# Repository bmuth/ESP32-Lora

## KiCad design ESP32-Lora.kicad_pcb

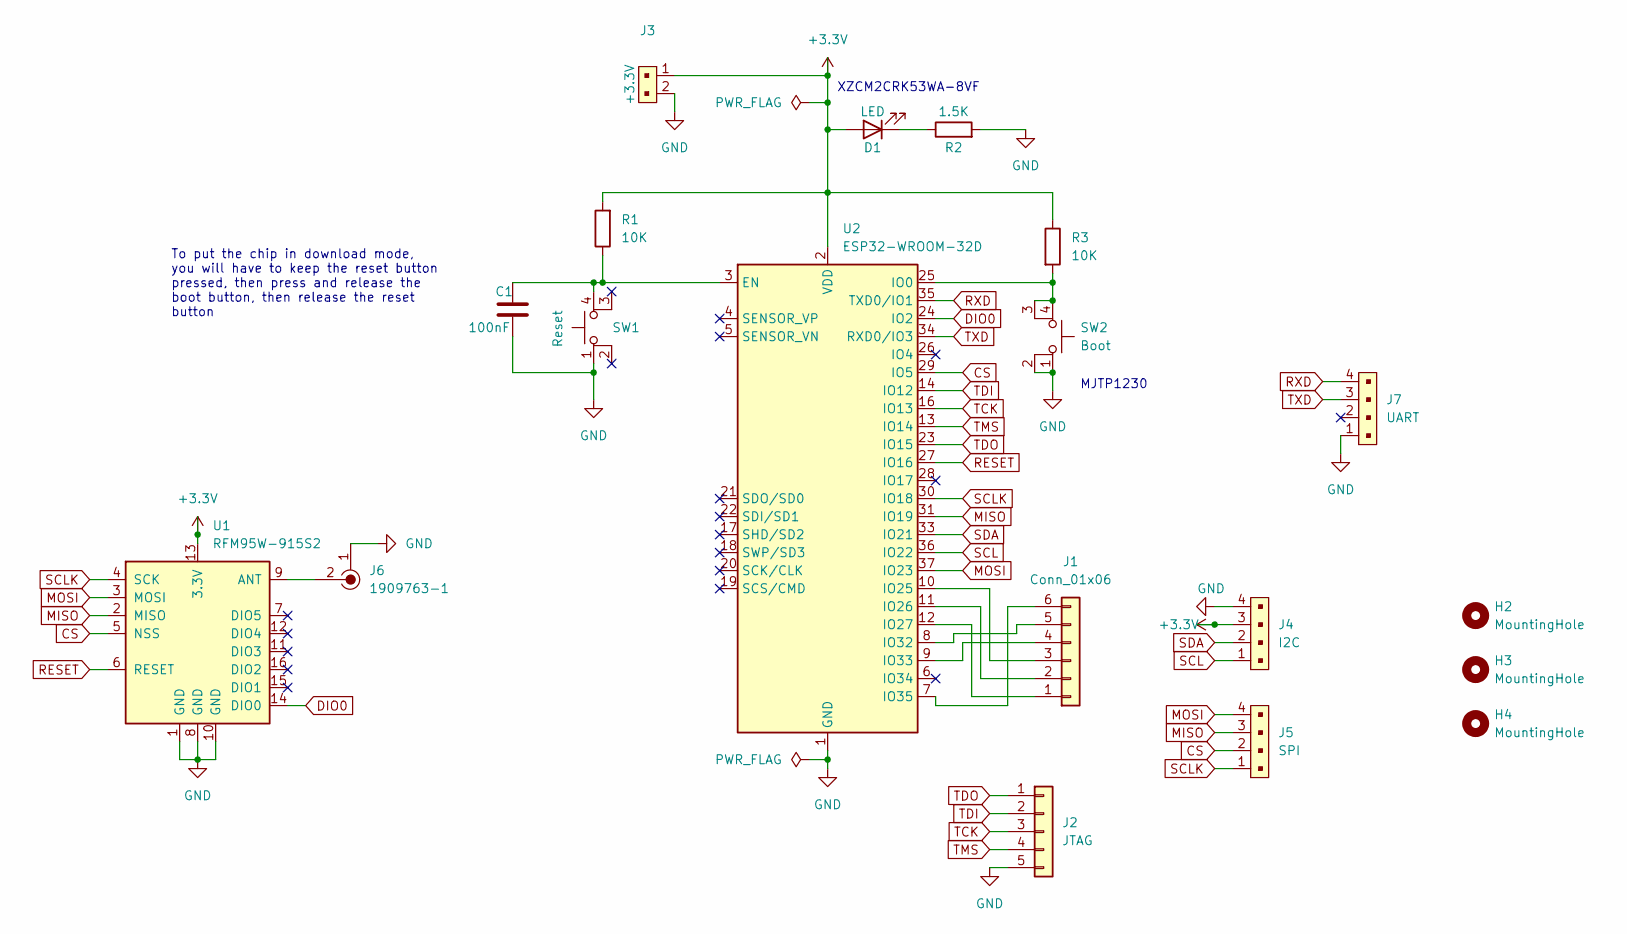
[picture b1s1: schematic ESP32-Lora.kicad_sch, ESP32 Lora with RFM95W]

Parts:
C1: 100nF; C_0805_2012Metric_Pad1.18x1.45mm_HandSolder
D1: LED; LED XZCM2CRK53WA
H2, H3, H4: MountingHole; MountingHole_2.2mm_M2
J1: Conn_01x06; PinHeader_1x06_P2.54mm_Vertical
J2: JTAG; PinHeader_1x05_P2.54mm_Vertical
J3: +3.3V; PinHeader_1x2_P2mm_Drill1mm; MPN B2B-PH-K-S(LF)(SN); Digi-Key_PN 455-1704-ND
J4: I2C; PinHeader_1x4_P2mm_Drill1mm; MPN B4B-PH-K-S(LF)(SN); Digi-Key_PN 455-1706-ND
J5: SPI; PinHeader_1x4_P2mm_Drill1mm; MPN B4B-PH-K-S(LF)(SN); Digi-Key_PN 455-1706-ND
J6: 1909763-1; Coax_Conn_U.FL; MPN 1909763-1; Digi-Key_PN A118077CT-ND
J7: UART; PinHeader_1x4_P2mm_Drill1mm; MPN B4B-PH-K-S(LF)(SN); Digi-Key_PN 455-1706-ND
R1, R3: 10K; R_0805_2012Metric_Pad1.20x1.40mm_HandSolder
R2: 1.5K; R_0805_2012Metric_Pad1.20x1.40mm_HandSolder
SW1: Reset; SW_PUSH_6.5mm_4.5mm
SW2: Boot; SW_PUSH_6.5mm_4.5mm
U1: RFM95W-915S2; XCVR_RFM95W-868S2
U2: ESP32-WROOM-32D; ESP32-WROOM-32

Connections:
+3V3: D1.2 (A), J3.1, J4.3, R1.2, R3.1, U1.13 (3.3V), U2.2 (VDD)
CS: J5.2, U1.5 (NSS), U2.29 (IO5)
DIO0: U1.14 (DIO0), U2.24 (IO2)
GND: C1.2, J2.5, J3.2, J4.4, J6.1, J7.1, R2.2, SW1.1, SW2.1, SW2.2, U1.1 (GND), U1.8 (GND), U1.10 (GND), U2.1 (GND), U2.15 (GND), U2.38 (GND), U2.39 (GND)
MISO: J5.3, U1.2 (MISO), U2.31 (IO19)
MOSI: J5.4, U1.3 (MOSI), U2.37 (IO23)
unnamed: C1.1, R1.1, SW1.4 (A), U2.3 (EN)
unnamed: D1.1 (K), R2.1
unnamed: J1.1, U2.12 (IO27)
unnamed: J1.2, U2.11 (IO26)
unnamed: J1.3, U2.10 (IO25)
unnamed: J1.4, U2.9 (IO33)
unnamed: J1.5, U2.8 (IO32)
unnamed: J1.6, U2.7 (IO35)
unnamed: J6.2, U1.9 (ANT)
unnamed: R3.2, SW2.3 (K), SW2.4 (A), U2.25 (IO0)
RESET: U1.6 (RESET), U2.27 (IO16)
RXD: J7.4, U2.35 (TXD0/IO1)
SCL: J4.1, U2.36 (IO22)
SCLK: J5.1, U1.4 (SCK), U2.30 (IO18)
SDA: J4.2, U2.33 (IO21)
TCK: J2.3, U2.16 (IO13)
TDI: J2.2, U2.14 (IO12)
TDO: J2.1, U2.23 (IO15)
TMS: J2.4, U2.13 (IO14)
TXD: J7.3, U2.34 (RXD0/IO3)

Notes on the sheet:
XZCM2CRK53WA-8VF
MJTP1230
To put the chip in download mode, you will have to keep the reset button pressed, then press and release the boot button, then release the reset button

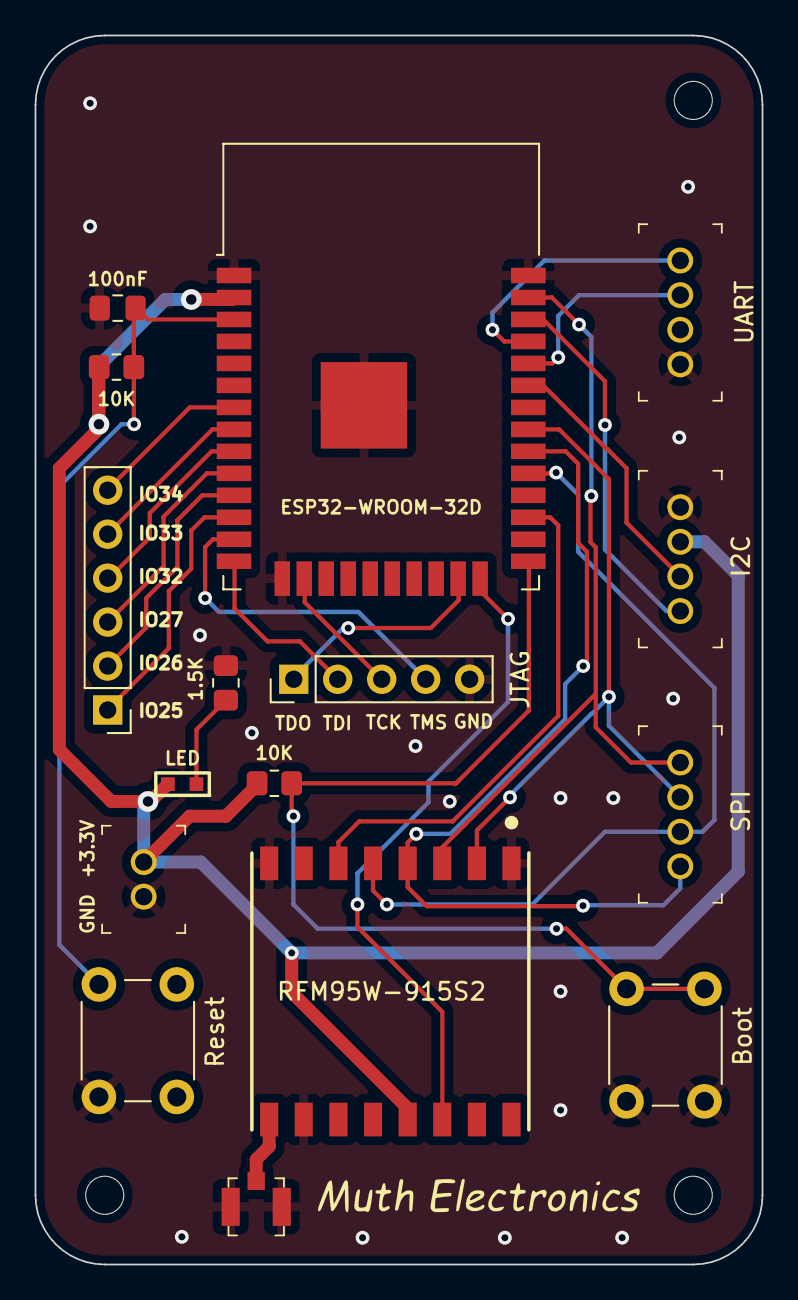
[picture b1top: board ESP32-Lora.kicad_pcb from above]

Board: 2 copper layers, 42.0 x 71.0 mm, 19 parts (0 on the bottom side), 26 nets.

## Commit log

2022-04-17 Version 1
